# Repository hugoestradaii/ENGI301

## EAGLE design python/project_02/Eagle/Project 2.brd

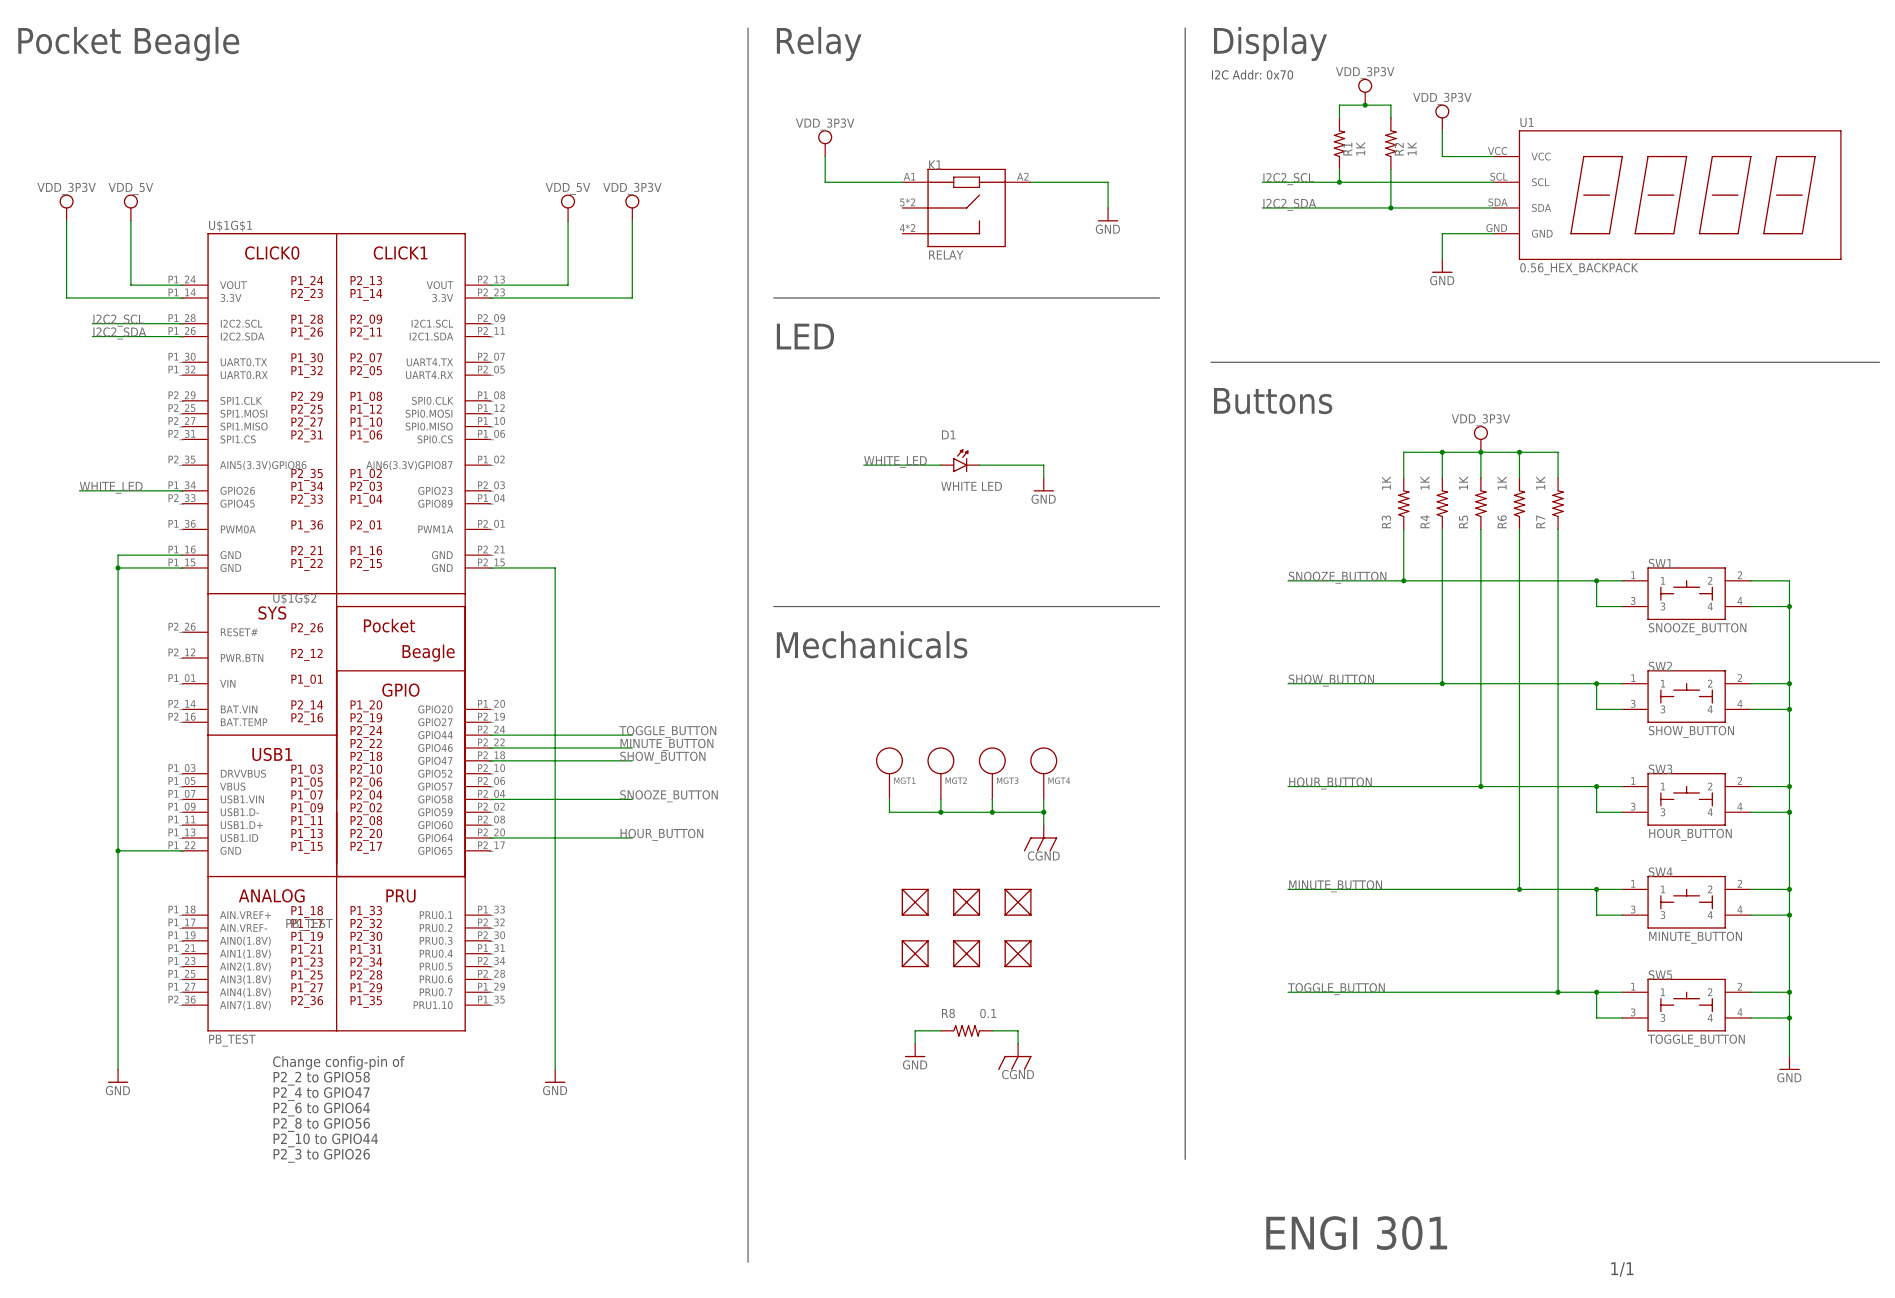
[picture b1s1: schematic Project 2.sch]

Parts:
D1: WHITE LED; EIA-STD
FUD1, FUD2, FUD3, FUD4, FUD5, FUD6: FIDUCIAL; FIDUCIAL_40MIL
K1: RELAY; RELAY_1-1415898-4
MGT1, MGT2, MGT3, MGT4: MOUNTING_HOLE
R1, R2, R3, R4, R5, R6, R7: 1K; R0603
R8: 0.1; R0805
SW1: SNOOZE_BUTTON; BUTTON_12.5MM
SW2: SHOW_BUTTON; BUTTON_12.5MM
SW3: HOUR_BUTTON; BUTTON_12.5MM
SW4: MINUTE_BUTTON; BUTTON_12.5MM
SW5: TOGGLE_BUTTON; BUTTON_12.5MM
U1: 0.56_HEX_BACKPACK
U$1: PB_TEST; POCKETBEAGLE

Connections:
BAT.VIN: U$1.P2_14 (BAT.VIN)
CGND: MGT1.P$1, MGT2.P$1, MGT3.P$1, MGT4.P$1, R8.2
GND: D1.CATHODE, K1.A2, R8.1, SW1.2, SW1.4, SW2.2, SW2.4, SW3.2, SW3.4, SW4.2, SW4.4, SW5.2, SW5.4, U1.GND, U$1.P1_15 (GND), U$1.P1_16 (GND), U$1.P1_22 (GND), U$1.P2_15 (GND), U$1.P2_21 (GND)
HOUR_BUTTON: R5.1, SW3.1, SW3.3, U$1.P2_20 (GPIO64)
I2C2_SCL: R1.1, U1.SCL, U$1.P1_28 (I2C2.SCL)
I2C2_SDA: R2.1, U1.SDA, U$1.P1_26 (I2C2.SDA)
MINUTE_BUTTON: R6.1, SW4.1, SW4.3, U$1.P2_22 (GPIO46)
SHOW_BUTTON: R4.1, SW2.1, SW2.3, U$1.P2_18 (GPIO47)
SNOOZE_BUTTON: R3.1, SW1.1, SW1.3, U$1.P2_04 (GPIO58)
TOGGLE_BUTTON: R7.1, SW5.1, SW5.3, U$1.P2_24 (GPIO44)
VDD_3P3V: K1.A1, R1.2, R2.2, R3.2, R4.2, R5.2, R6.2, R7.2, U1.VCC, U$1.P1_14 (3.3V), U$1.P2_23 (3.3V)
VDD_5V: U$1.P1_24 (VOUT), U$1.P2_13 (VOUT)
VIN: U$1.P1_01 (VIN)
WHITE_LED: D1.ANODE, U$1.P1_34 (GPIO26)

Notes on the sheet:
Pocket Beagle
Buttons
Display
Relay
I2C Addr: 0x70
1/1
ENGI 301
LED
Mechanicals
Change config-pin of P2_2 to GPIO58 P2_4 to GPIO47 P2_6 to GPIO64 P2_8 to GPIO56 P2_10 to GPIO44 P2_3 to GPIO26

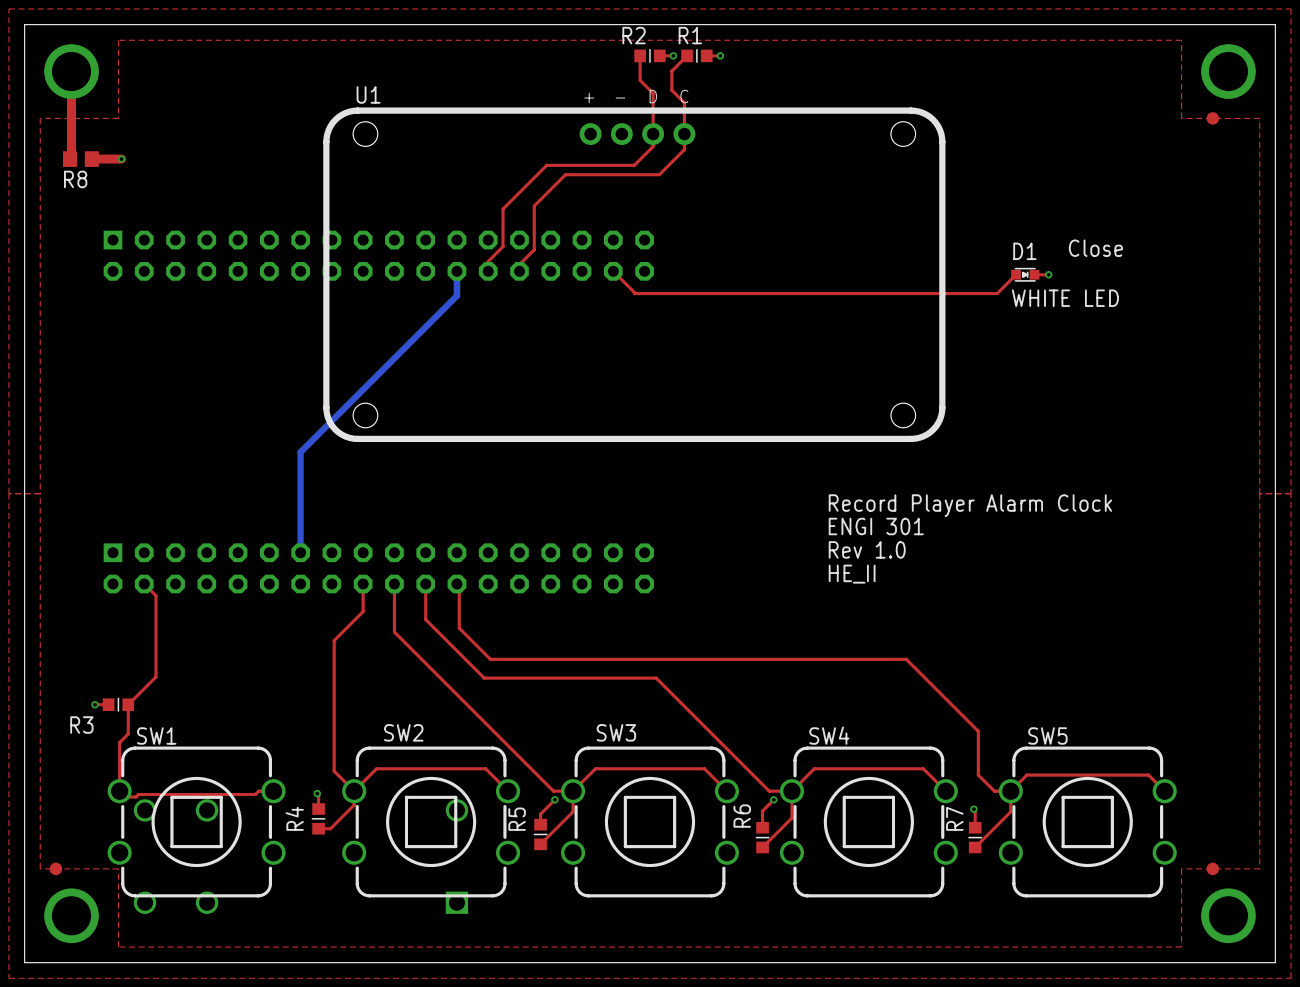
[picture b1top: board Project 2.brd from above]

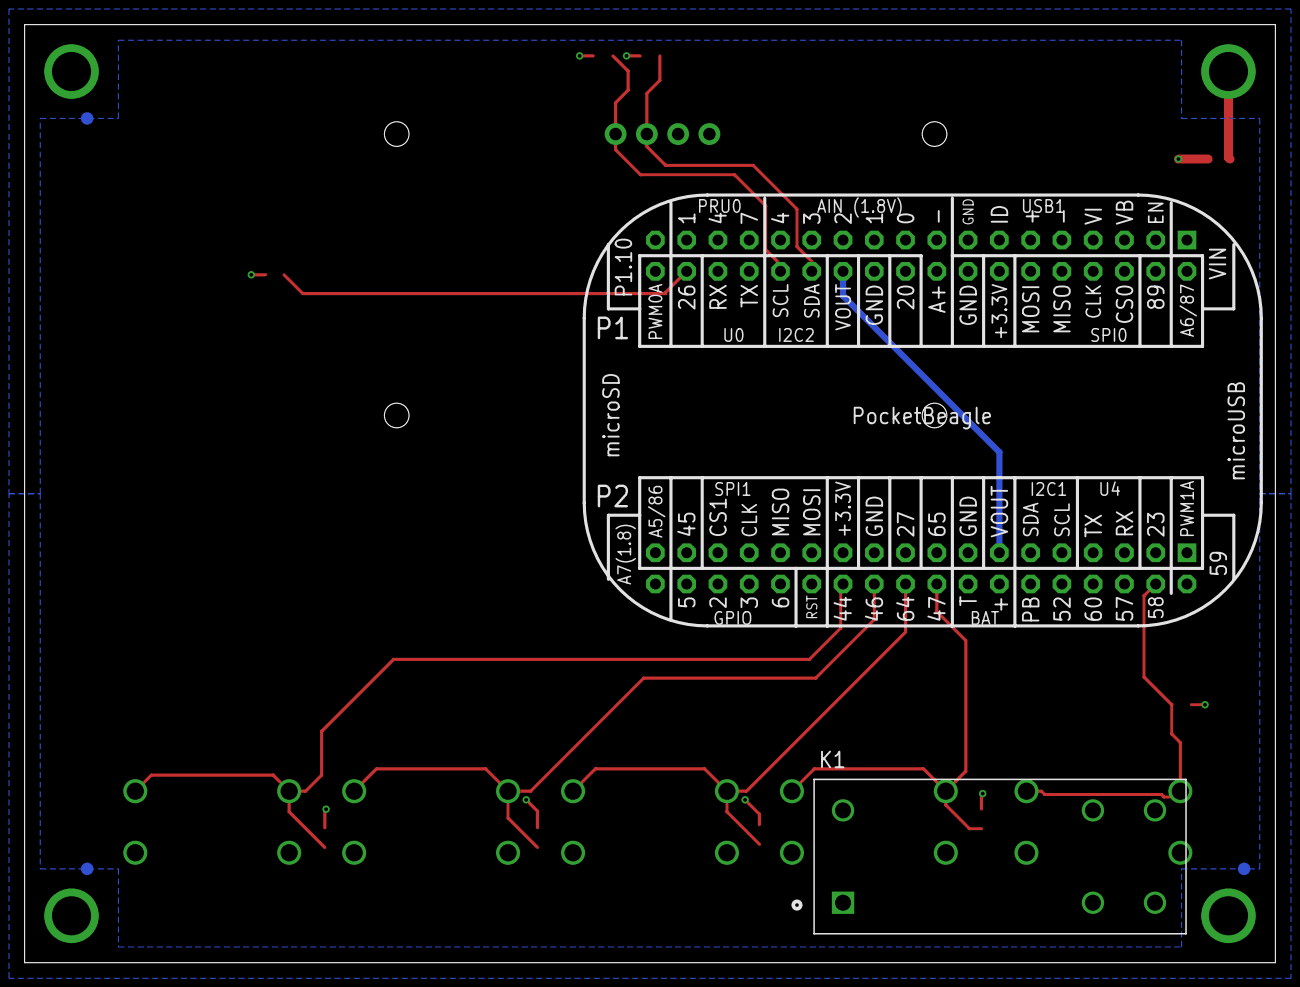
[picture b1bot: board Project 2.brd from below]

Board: 4 copper layers, 101.6 x 76.2 mm, 27 parts (5 on the bottom side), 12 nets.

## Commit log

2021-09-16 Updating README.md
2021-10-05 My first code :') Adding Simple_calc.py
2021-10-05 Adding blink_USR3.py
2021-11-09 Adding Project 01 Code
2021-11-09 Updating README
    Adding Hackster.io Page URL
2021-11-17 Creating Directories
2021-12-14 Uploaded Files regarding Project 2
2021-12-14 Uploading Gerber Pics
